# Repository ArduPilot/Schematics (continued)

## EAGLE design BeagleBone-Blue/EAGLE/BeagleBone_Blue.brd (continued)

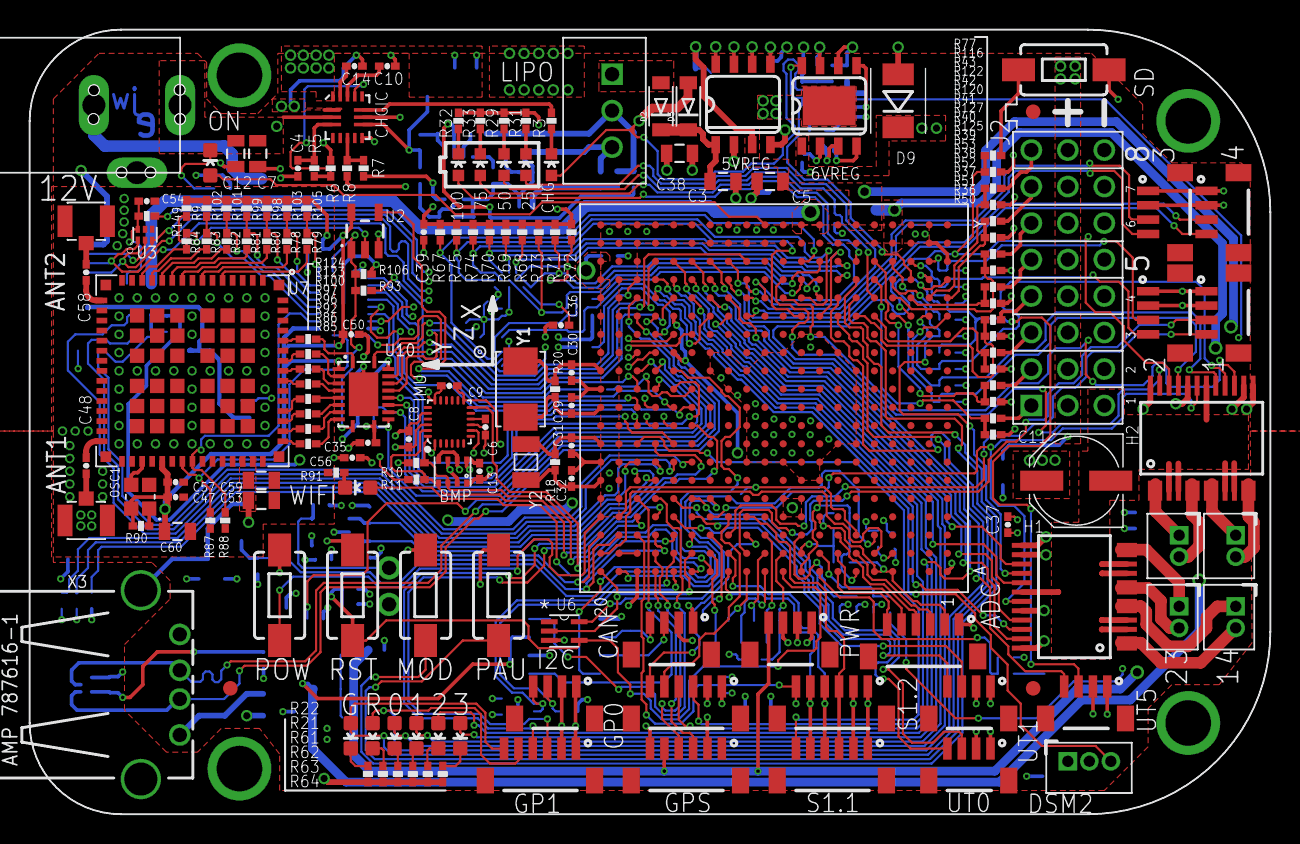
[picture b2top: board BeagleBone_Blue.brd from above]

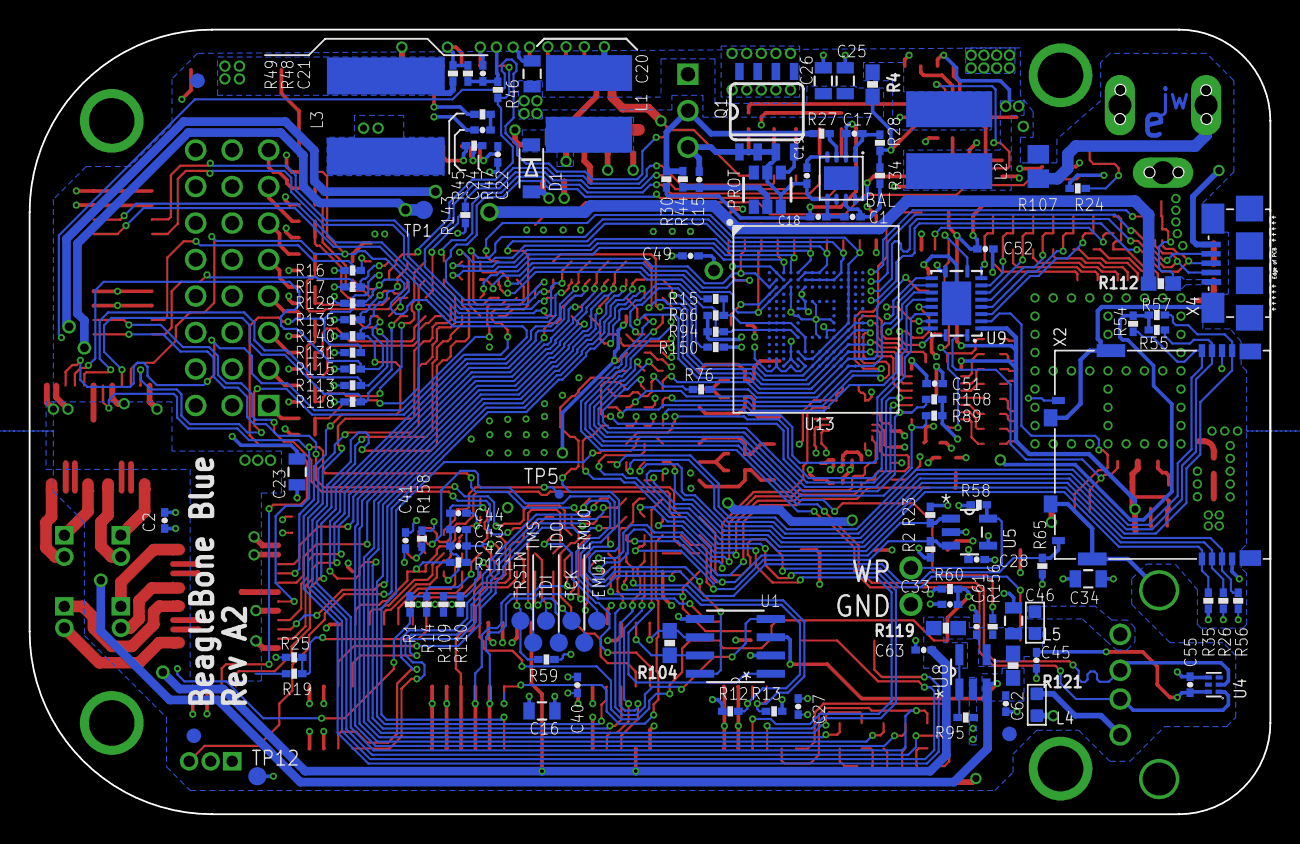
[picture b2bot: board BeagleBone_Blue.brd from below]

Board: 4 copper layers, 86.4 x 54.6 mm, 302 parts (122 on the bottom side), 268 nets.

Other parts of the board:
BOARD: BEAGLEBONE_BLUE_NO_HOLES
U$2: BATTERY_INDICATOR_LEFT
U$5: XYZ_BIG

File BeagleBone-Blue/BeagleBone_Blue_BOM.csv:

Qty,Value,Parts,Device,Package,Description,MANUFACTURER AND PART NUMBER,Temperature range / Celsius,
5,BLUE,"0, 1, 2, 3, ON",LED0603,LED-0603,LEDs,Lite-On LTST-C191TBKT,-20..80,
1,PJ-102B_POWER_CON,12V,PJ-102B_POWER_CON,PJ-102B_POWER_CON,,"CUI PJ-102B, MT CONN DC630-20D",,
1,AP1509SOIC-8-TIGHT,5VREG,AP1509SOIC-8-TIGHT,SO08-TIGHT,"150KHz, 2A PWM BUCK DC/DC CONVERTER",Diodes Inc. AP1509-50SG-13,-20..85,
1,AOZ1284,6VREG,AOZ1284,SO08-EXPOSED,,Alpha & Omega Semiconductor AOZ1284PI,-40..85,
6,JST_SH_6,"ADC, GP0, GP1, GPS, S1.1, S1.2",JST_SH_6,JST_SH_6,,"JST BM06B-SRSS-TB(LF)(SN), MT CONN WTB10-06-02-2",,
2,U.FL-R-SMT-1(10),"ANT1, ANT2",U.FL-R-SMT-1,U.FL-R-SMT-1,,"Hirose U.FL-R-SMT-1(10), MT CONN JTIX-20279",,
2,RED,"B0, R",LED0603,LED-0603,LEDs,"Everlight 19-21SURC/S530-A3/TR8, Everlight 19-217/R6C-AL1M2VY/3T",,
6,GREEN,"B1, B2, B3, CHG, G, WIFI",LED0603,LED-0603,LEDs,"Everlight 19-21SYGC/S530-E2/TR8, Everlight 19-217/GHC-YR1S2/3T",,
1,BQ29209,BAL,BQ29209,8-SON_3X3MM,BQ29209 2-CELL Balance and Overvoltage Protection,Texas Instruments BQ29209DRBR,-40..110,
1,BMP280,BMP,BMP280,BMP280,BOSCH BMP280 Digital Pressure Sensor,Bosch BMP280,-40..85,
32,0.1uF,"C1, C2, C6, C8, C9, C13, C14, C15, C17, C18, C19, C21, C22, C24, C27, C28, C35, C37, C39, C40, C41, C43, C44, C45, C47, C49, C50, C51, C52, C54, C55, C56",CAP0402-CAP,0402-CAP,Capacitor,"Samsung CL05A104MP5NNNC, Kemet C0402C104K9PACTU, Murata GRM155R71C104KA88D",-55..85,
1,100uF 16V,C11,CPOL-USD,PANASONIC_D,"POLARIZED CAPACITOR, American symbol","LELON VES101M1CTR-0605, United Chemi-Con EMVA160ADA101MF55G",-40..85,
6,10pF,"C29, C30, C31, C32, C48, C58",CAP0402-CAP,0402-CAP,Capacitor,Yaego CC0402JRNPO9BN100,-55..125,
15,10uF,"C3, C5, C7, C12, C16, C20, C23, C25, C26, C34, C38, C46, C53, C59, C60",CAP0805,805,Capacitor,Murata GRM219R61E106KA12D,-55..85,
2,2.2uF,"C33, C36",CAP0402-CAP,0402-CAP,Capacitor,"TDK C1005X5R0J225K050BC, Murata GRM155R60J225ME15D",-55..85,
4,1uF,"C4, C10, C57, C61",CAP0402-CAP,0402-CAP,Capacitor,"Samsung CL05A105KO5NNNC, Taiyo Yuden JMK105BJ105KV-F, Murata GRM155R60J105KE19D",-55..85,
1,1nF,C42,CAP0402-CAP,0402-CAP,Capacitor,Murata GRM155R71H102KA01D,-55..85,
2,0.22uF,"C62, C63",CAP0402-CAP,0402-CAP,Capacitor,Murata GRM155R71C224KA12D,-55..125,
10,JST_SH_4,"CAN, E1, E2, E3, E4, I2C, PWR, UT0, UT1, UT5",JST_SH_4,JST_SH_4_SMD,,"JST BM04B-SRSS-TB(LF)(SN), MT CONN WTB10-04-02-2",-25..85,
1,MP2615,CHGIC,MP2615,MP2615,,Monolithic Power Systems MP2615GQ-Z,-40..85,
3,,"D1, D2, D3",DIODESOD-123,SOD-123,Diode,ON Semiconductor MBR230LSFT1G,-55..125,
1,,D9,DIODEDO214AA,DO-214AA,Diode,Vishay SSB44-E3/52T,-65..150,
1,JST_ZH_3,DSM2,JST_ZH_3,JST_ZH_3,,"JST B3B-ZR(LF)(SN), MT CONN WB150SL-03SR03",,
2,TB6612FNG,"H1, H2",TB6612FNG,SSOP24,Toshiba 1A motor driver,"Toshiba TB6612FNG(O,C8,EL)",-20..85,
1,MPU-9250,IMU,MPU-9250,QFN24G-0.4-3X3MM,314990005,Invensense MPU-9250,-40..105,
1,SERVO_HEADERS_8X,J2,SERVO_HEADERS_8X,3X8_0.1_HEADER,,"Preci-Dip 894-80-024-10-001101, Samtec THTSW-108-08-F-T, ??? JTP254-D180-308-001-T",-55..105,
2,6.8uH,"L1, L2",INDUCTORBOURNS_SRN6045,SRN6045,Inductors,Taiyo Yuden NRS6045T6R3MMG,-40..125,
1,3.6 uH,L3,INDUCTOR,8X8MM_INDUCTOR,Inductors,Taiyo Yuden NRS8040T3R6NJGJ,-25..120,
2,120,"L4, L5",INDUCTOR/FERRITE-BEAD'0603',L0603,,"Laird LI0603G121R-10, Murata BLM18AG121SN1D",-55..125,
1,BATTERY,LIPO,JST_XH_3-PIN,JST_XH_3-PIN,,"MT CONN WB250SV-03SBD03, JST B3B-XH-A(LF)(SN)",-25..85,
4,JST_ZH_2,"M1, M2, M3, M4",JST_ZH_2,JST_ZH_2,,"MT CONN WB150SV-02SBD03, JST B2B-ZR(LF)(SN)",-25..85,
5,SWITCH-MOMENTARY-2SMD-1101NE,"MOD, PAU, POW, RST, SD",SWITCH-MOMENTARY-2SMD-1101NE,TACTILE-SWITCH-1101NE,"Various NO switches- pushbuttons, reed, etc",C&K Components RS-032G05A3-SM RT,-20..70,
1,NZ2520SB-32.768KHZ-NSA3534C,OSC1,OSCILLATOR,NZ2520S,,"NDK NZ2520SB-32.768KHZ-NSA3534C, Interquip 1651-L3273-BTKQYA",-40..85,
1,S-8261,PROT,S-8261,SOT-236,,Seiko S-8261AAJMD-G2JT2G,-40..85,
1,MOSFET-N,Q1,MOSFET-NCHANNEL,SO08-TIGHT,Common NMOSFET Parts,Vishay Siliconix SI4778DY-T1-GE3,-55..150,
1,47k,"R45",RESISTOR0402-RES,0402-RES,Resistor,Yaego RC0402JR-0747KL,-55..155,
2,"47k 1%","R1, R19",RESISTOR0402-RES,0402-RES,Resistor,Yaego RC0402FR-0747KL,-55..155,
1,"120, DNP",R104,RESISTOR0603,0603-RES,Resistor,N/A,,
1,".1, 0805",R107,R-US_R0805,R0805,"RESISTOR, American symbol",Yaego RL0805JR-070R1L,-55..125,
3,0,"R111, R149, R150",RESISTOR0402-RES,0402-RES,Resistor,Yaego RC0402JR-070RL,-55..155,
1,0,R112,RESISTOR0603,0603-RES,Resistor,Yaego RC0603JR-070RL,-55..155,
2,"0, DNP","R119, R121",RESISTOR0603,0603-RES,Resistor,,,
20,33,"R15, R76, R77, R78, R79, R80, R81, R82, R83, R84, R85, R86, R92, R93, R96, R97, R100, R123, R124, R156",RESISTOR0402-RES,0402-RES,Resistor,Yaego RC0402JR-0733RL,-55..155,
18,100k,"R16, R17, R47, R87, R88, R113, R115, R116, R118, R120, R122, R125, R127, R129, R131, R135, R140, R143",RESISTOR0402-RES,0402-RES,Resistor,"Samsung RC1005J104CS, Yaego RC0402JR-07100KL",-55..155,
2,1M,"R18, R20",RESISTOR0402-RES,0402-RES,Resistor,Yaego RC0402JR-071ML,-55..155,
4,1.5K,"R2, R23, R58, R106",RESISTOR0402-RES,0402-RES,Resistor,Yaego RC0402JR-071K5L,-55..155,
8,240,"R21, R22, R29, R30, R31, R32, R33, R91",RESISTOR0402-RES,0402-RES,Resistor,Yaego RC0603JR-07240RL,-55..155,
30,10K,"R5, R6, R8, R26, R35, R48, R54, R55, R56, R57, R60, R65, R66, R67, R68, R69, R70, R71, R72, R73, R74, R75, R94, R98, R99, R101, R102, R103, R105, R158",RESISTOR0402-RES,0402-RES,Resistor,"Samsung RC1005J103CS, Yaego RC0402JR-0710KL",-55..155,
3,150,"R27, R28, R34",RESISTOR0402-RES,0402-RES,Resistor,Yaego RC0402JR-07150RL,-55..155,
8,1k,"R3, R44, R46, R61, R62, R63, R64, R90",RESISTOR0402-RES,0402-RES,Resistor,"Samsung RC1005J102CS, Yaego RC0402JR-071KL",-55..155,
1,0.1,R4,RESISTOR0603,0603-RES,Resistor,"Samsung RU1608FR100CS, Yaego RL0603FR-070R1L",-55..155,
1,64.9k,R49,RESISTOR0402-RES,0402-RES,Resistor,Samsung RC1005F6492CS,-55..155,
21,4.7k,"R7, R10, R11, R12, R13, R24, R36, R37, R38, R39, R40, R41, R42, R43, R50, R51, R52, R53, R59, R109, R110",RESISTOR0402-RES,0402-RES,Resistor,"Samsung RC1005F2610CS, Yaego RC0402JR-074K7L",-55..155,
2,"4.7k 1%","R14, R25",RESISTOR0402-RES,0402-RES,Resistor,"Samsung RC1005F2610CS, Yaego RC0402FR-074K7L",-55..155,
2,"1K, DNP","R89, R108",RESISTOR0402-RES,0402-RES,Resistor,N/A,,
1,"10K, DNP",R9,RESISTOR0402-RES,0402-RES,Resistor,N/A,,
1,OSD3358,SIP,OSD3358,OSD3358,Octavo Systems LLC - OSD3358 Rev A,Octavo Systems OSD3358-512M-BAS,0..85,
1,TCAN1051HV,U1,TCAN1051HV,D8,CAN Transceiver,Texas Instruments TCAN1051HVD,-40..125,
1,EMMC,U13,EMMC04G-S100-B08U,MICRON_EMMC_153,,"Micron MTFC4GACAJCN-1M WT, Kingston EMMC04G-S100-B08U",-40..85,
1,SN74LV1T126DBVR,U2,SN74LV1T126DBVR,SOT23-5,,Texas Instruments SN74LV1T126DBVR,-40..125,
2,TPD4S012DRY,"U3, U4",TPD4S012DRYR,SON-6(TI)-DRY,,Texas Instruments TPD4S012DRYR,-40..85,
1,24LC_32AT-I/OT,U5,24LC_32AT-I/OT,SOT95P290X145-5N,"IC, I2C Serial EEPROM,SOT-23-5",Microchip 24LC32AT-I/OT,-40..125,
1,SN74LVC1G07_DCK_5,U6,SN74LVC1G07_DCK_5,DCK5,Single Buffer/Driver With Open-Drain Output,Texas Instruments SN74LVC1G07DCKR,-40..125,
1,WL1835MODGBMOCR,U7,WL1835MOD,MOC-100(TI),,Texas Instruments WL1835MODGBMOCR,-20..70,
1,TPS2105_DBV_5,U8,TPS2105_DBV_5,DBV5,,Texas Instruments TPS2105DBVR,-40..85,
2,TXS0108ERGYR,"U9, U10",TXS0108ERGYR,R-PVQFN-N20(TI),,Texas Instruments TXS0108ERGYR,-40..85,
1,SCHA5B0200,X2,SCHA5B0200(ALPS_USD),SCHA5B0200,,Alps SCHA5B0200,-20..70,
1,USB1,X3,USB_HOST_W/CHASSIS_GND,USB_HOST_HORIZONTAL_W/CHASSIS_GND,,"TE Connectivity / AMP 787616-1-P, ??? UBAF-1202",-55..85,
1,10118192-0001LF,X4,10118192-0001LF,10118192-0001LF(MICRO-USB-B-AMPHENOL-FCI),Amphenol FCI Micro USB Type B Complete Surface Mount (SMT) no guide holes,"FCI 10118192-0001LF, ??? UBAF-0608",-30..80,
1,24 MHz,Y1,CRYSTAL_5X3.2MM,CRYSTAL_5X3.2MM,,"CTS 445A35A24M00000, TXC 7A-24.000MAAJ-T",-40..85,
1,32.768kHz,Y2,CRYSTAL_3.2X1.5,CRYSTAL_3.2X1.5,,Fox Electronics FX135A-327,-20..70,
2,2.4GHz antenna,,,,,"Anaren 66089-2406, Gptech GPRC01113-CE0030B5",,

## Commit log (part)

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2018-07-10 added ProfiCNC/Cube
    with thanks to Philip Rowse
2018-07-10 added CUAV schematics
2018-07-10 added 3DR schematics
2018-07-31 added mRobotics boards
2019-11-11 Add new board schematics for Revo, Sparky, and F4BY
2019-11-14 add beaglebone and FMUv4 schematics
2019-11-27 add mRo UAVCAN Node schematics
2020-07-03 Add Holybro PIX32v5 files
2020-07-04 remove docs
2020-07-13 Re-add Holybro docs with their approval
2020-10-09 added Holybro schematics
2020-10-09 old holybro files removed
    now in Holybro directory
2020-10-09 more CUAV schematics
2021-02-07 added pinouts for Durandal
2022-03-22 Add a datasheets folder, populate with novatel documentation
    Novatel data sheet was pulled from the wayback machine, and is the
    linked datasheet from the novatel GPS driver
2022-04-04 add files for esp32imu_module_v11 ArduPilot target
2022-05-18 Carrier Board Approval
2022-07-13 Change board license list to link on OEM page
2023-09-05 removed files at request of vendor
2023-11-30 Add Blue Robotics Navigator schematics
2024-04-12 Add NxtPX4v2 PCB files
2025-01-20 add CUAV license document
2025-04-15 update schematics, remove unused files
2026-04-29 ZeroOne: add FPGA code used as frontend for SCH16T
2026-05-13 Add Titan Dynamics (Mohammad Adib) carrier board footprint license entry
2026-06-29 Add schematics for GPILOT_P1
